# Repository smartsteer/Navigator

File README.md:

# SmartSteer Navigator

Aplikacja do prowadzenia równoległego i autosterowania ciągnika, zgodna z płytkami AgOpenGPS (AIO).
Jeden kod w Kotlinie daje dwie wersje:

- **Android** — tablet w kabinie (APK),
- **Windows** — komputer / tablet z Windows (instalator `.msi` / `.exe`).

## Jak to działa

Aplikacja liczy geometrię prowadzenia (linia AB, krzywe, pure pursuit) i co ok. 100 ms wysyła
zadany kąt skrętu do modułu na płytce. Regulację silnika (PID, PWM) i odczyt czujnika kąta kół
robi oryginalny firmware AgOpenGPS na płytce — nie jest zmieniany.

Komunikacja: UDP w sieci `192.168.5.x`, aplikacja nasłuchuje na porcie **9999**, wysyła na **8888**.
Ramka: `0x80 0x81 źródło PGN długość dane… CRC`.

| PGN | Kierunek | Treść |
|-----|----------|-------|
| 254 | aplikacja → moduł skrętu | prędkość, autoster wł./wył., kąt zadany, odległość od linii, sekcje |
| 253 | moduł skrętu → aplikacja | kąt rzeczywisty, kurs/przechył IMU, przełączniki, PWM |
| 252 / 251 | aplikacja → moduł skrętu | ustawienia i konfiguracja sterowania |
| 239 | aplikacja → moduł maszyny | sekcje, podnośnik, zawrót |

### Podłączenie tabletu z Androidem

Przejściówka USB‑C → Ethernet (najlepiej hub z ładowaniem PD) albo Wi‑Fi przez mały router
w kabinie. Router powinien rozdawać adresy (DHCP) w sieci `192.168.5.x`.

## Struktura

```
composeApp/
  src/commonMain/   wspólny kod: logika (core/) i ekrany (Compose Multiplatform)
  src/androidMain/  start aplikacji na Androidzie
  src/desktopMain/  start programu na Windowsie
  src/commonTest/   testy
```

## Budowanie

- Android: `./gradlew :composeApp:assembleDebug`
- Windows (na Windowsie): `./gradlew :composeApp:packageMsi`
- Uruchomienie na komputerze bez instalacji: `./gradlew :composeApp:run`
- Testy: `./gradlew :composeApp:desktopTest`

GitHub Actions budują APK i instalator Windows przy każdym pushu — pliki są w zakładce
**Actions → ostatni przebieg → Artifacts**.

## Plan

1. Rdzeń: odczyt NMEA, linia AB, odchyłka, symulator jazdy
2. Autosterowanie: pure pursuit, PGN 254/253, ekran diagnostyki
3. Sekcje i mapa pokrycia, zawroty, granice pól
4. Integracja z WAR (mapy aplikacyjne, ewidencja zabiegów)

## Licencja

GNU General Public License v3.0 (GPLv3). Projekt korzysta z rozwiązań i algorytmów AgOpenGPS
(© Brian Tischler i współtwórcy, GPLv3) — fragmenty przeniesione z AgOpenGPS są oznaczone w kodzie.
Program rozpowszechniany jest z kodem źródłowym, na tej samej licencji.

WAR (Wirtualny Asystent Rolnika) jest osobnym programem i nie jest objęty tą licencją —
wymienia dane z Navigatorem przez interfejs (mapy dawek, ewidencja zabiegów).

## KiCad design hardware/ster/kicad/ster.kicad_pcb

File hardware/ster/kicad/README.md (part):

# Płytka Ster — schemat jako kod (etap 15b)

Schemat płytki Ster w SKiDL → netlista KiCad. Specyfikacja: [`../README.md`](../README.md). Licencja GPLv3.
Na podstawie AgOpenGPS (© Brian Tischler i współtwórcy, GPLv3), pliki `TeensyModules/AIO Standard v4/PCB Build/AIO v4.5 Std/`
(PCB EasyEDA, „Ampseal pinout.jpg”) i `TeensyModules/AIO v4 Firmware/` z github.com/AgOpenGPS-Official/Boards.

| Plik | Co to |
|---|---|
| `ster.py` | schemat — źródło prawdy; `pip install skidl==1.2.3`, potem `python3 ster.py` → `ster.net` (bez bibliotek KiCad — wszystkie części zdefiniowane w kodzie) |
| `ster.net` | netlista KiCad (248 części, 208 sieci) do 15c |
| `imxrt1062_kulki.csv` | wszystkie 196 kulek MIMXRT1062 (MAPBGA‑196): kulka, sygnał, pin Teensy 4.1 |
| `bga196.py` → `smartsteer_ster.pretty` | obudowa MAPBGA‑196 12 × 12 mm / 0,8 mm (pola NSMD 0,40 mm); reszta obudów z bibliotek KiCad 7 |
| `place.py` | obrys 110 × 80 mm, 4 warstwy, rozmieszczenie (etap 15c1) |
| `netclass.py` | klasy połączeń: Default 0,15/0,127 mm (przelotka 0,45/0,2), Moc 1,2 mm, Zasilanie 0,4 mm, RF 0,35 mm, USB 0,2 mm |
| `ster.kicad_pcb`, `ster.kicad_pro` | płytka: części rozmieszczone, płaszczyzny In1 = GND, In2 = V3V3_STER; **bez ścieżek** (15c2) |

Kolejność (narzędzia: `../../narzedzia/README.md`): `ster.py` → `kinet2pcb -i ster.net -w -l .` → `netclass.py` → `place.py`
→ `plaszczyzny.py ster.kicad_pcb In1.Cu:GND In2.Cu:V3V3_STER` → (15c2) wyprowadzenie BGA, Freerouting, `dotrasuj.py`, wylewki mocy,
`drc.py`, `fab_jlcpcb.py`.

`ster.py` przy każdym uruchomieniu sprawdza (assert): AMPSEAL 1:1 z AIO v4.5 Std (poza 13 i 19 — CAN Maszyna), piny
Teensy z firmware AIO na tych samych kulkach co w Teensy 4.1, wszystkie kulki zasilania i masy podłączone; ERC bez uwag.

**Mapa kulek** pochodzi z `bga_pinout_t41` (PJRC, w repozytorium SparkFun MicroMod Teensy) i jest zgodna z kartą NXP
IMXRT1060CEC (tabele 86–87) dla wszystkich 196 kulek. Rdzeń (DCDC 1,1 V, kondensatory, kwarce 24 MHz / 32 kHz, flash QSPI
na SD_B1, bootloader MKL02 na JTAG/POR_B/BOOT_MODE0, kluczowanie 3,3 V przez PMIC_ON_REQ) odtworzony z połączeń
otwartego projektu SparkFun MicroMod Teensy (CC BY-SA 4.0) — czyli tak jak w Teensy 4.x, więc Teensy Loader działa.

## AMPSEAL 23 — ta sama wiązka co AIO v4.5 Std

| Pin | AIO v4.5 Std | Ster |
|---|---|---|
| 1 | 5V WAS | 5 V czujnika kąta (PTC 100 mA) |
| 2 / 3 | WAS High / Low | ADS1115 AIN0 / AIN1 (5 V, adres 0x48) |
| 4, 21, 23 | GND | masa |
| 5 / 6 | LEFT / RIGHT (Cytron) | wyjścia mostka DRV8701E |
| 7 | LOCK | AOD4185 z 12 V (5 A), dioda gasząca |
| 8 / 9 | Steer / Work | transoptory → piny 32 / 34, przyciski serwisowe |
| 10 | Pres/Rem | zworka: Remote (pin 37, domyślnie) albo ciśnienie (A10) |
| 11 / 12 | A12 / A13 | piny 26 / 27 przez zworki (zwarte) |
| 13 | A14 | **zmiana:** domyślnie CAN „Maszyna” L; zworka 2‑3 → A14 (pin 38) jak AIO |
| 14 / 15 | Speed + / − | transoptor od pinu 36 (otwarty kolektor; zworki: podciągnięcie 12 V, minus do masy) |
| 16 / 17 | CAN H / L | CAN3 (ciągnik / Keya), terminator zworką |
| 18 | Alt cytron pwr | zasilanie mostka; zworka z 12 V zwarta (otworzyć przy osobnym przewodzie) |
| 19 | — (wolny) | **CAN „Maszyna” H** (CAN2, piny 0/1) |
| 20 | +12 V Board | 12 V za idealną diodą |
| 22 | +12 V in | wejście 12 V |

Silnik zostaje na **jednym styku na fazę** (5, 6) i zasilanie 18 — jak AIO, żeby wiązka pasowała (w 15a było „2 + 2”,
ale AMPSEAL 23 nie ma wolnych pinów). Sprawdzić prąd styku przy przekroju przewodu (lista niżej).

## Piny Teensy → pad i.MXRT (te używane na płytce)

| Pin Teensy | Pad i.MXRT | Kulka BGA | Na płytce Ster |
|---|---|---|---|
| 0 | GPIO_AD_B0_03 | G11 | CAN2 RX → MCP2562 „Maszyna” |
| 1 | GPIO_AD_B0_02 | M11 | CAN2 TX → MCP2562 „Maszyna” |
| 2 | GPIO_EMC_04 | F2 | PWM silnika → DRV8701E EN |
| 3 | GPIO_EMC_05 | G5 | LOCK (2N7002 → AOD4185) + zworka nSLEEP |
| 4 | GPIO_EMC_06 | H5 | kierunek → DRV8701E PH |
| 5 | GPIO_EMC_08 | H3 | dioda: zasilanie |
| 6 | GPIO_B0_10 | D9 | dioda: Ethernet |
| 7 | GPIO_B1_01 | B11 | Serial2 RX (zapas) |
| 8 | GPIO_B1_00 | A11 | Serial2 TX (zapas) |
| 9 | GPIO_B0_11 | A10 | dioda: GPS czerwona |
| 10 | GPIO_B0_00 | D7 | dioda: GPS zielona |
| 11 | GPIO_B0_02 | E8 | dioda: autoster czuwanie |
| 12 | GPIO_B0_01 | E7 | dioda: autoster aktywny |
| 13 | GPIO_B0_03 | D8 | dioda: GGA |
| 14 | GPIO_AD_B1_02 | L11 | Serial3 TX → radio RTK |
| 15 | GPIO_AD_B1_03 | M12 | Serial3 RX ← radio RTK |
| 18 | GPIO_AD_B1_01 | K11 | I²C SDA → ADS1115 (translator 5 V) |
| 19 | GPIO_AD_B1_00 | J11 | I²C SCL → ADS1115 |
| 20 | GPIO_AD_B1_10 | L13 | Serial5 TX → IMU |
| 21 | GPIO_AD_B1_11 | J13 | Serial5 RX ← IMU (TM171 / BNO085 RVC) |
| 24 | GPIO_AD_B0_12 | K14 | A10 ciśnienie (dzielnik 10k/20k, 4–20 mA zworką) |
| 26 | GPIO_AD_B1_14 | G12 | A12 ← AMPSEAL 11 |
| 27 | GPIO_AD_B1_15 | J14 | A13 ← AMPSEAL 12 |
| 28 | GPIO_EMC_32 | D5 | Serial7 RX ← ZED‑F9P TXD |
| 29 | GPIO_EMC_31 | C5 | Serial7 TX → ZED‑F9P RXD |
| 30 | GPIO_EMC_37 | E4 | CAN3 RX (ciągnik / Keya) |
| 31 | GPIO_EMC_36 | C3 | CAN3 TX |
| 32 | GPIO_B0_12 | C10 | STEERSW ← transoptor |
| 33 | GPIO_EMC_07 | H4 | nFAULT DRV8701E (nowe, firmware 17) |
| 34 | GPIO_B1_13 | D14 | WORKSW ← transoptor |
| 36 | GPIO_B1_02 | C11 | impuls prędkości → transoptor |
| 37 | GPIO_B1_03 | D11 | REMOTE ← transoptor |
| 38 | GPIO_AD_B1_12 | H12 | A14 ← AMPSEAL 13 (zworka 2‑3) |
| 41 | GPIO_AD_B1_05 | K12 | A17 prąd silnika (SO DRV8701E, 60 mV/A) |

Ethernet RMII jak Teensy 4.1: GPIO_B1_04…B1_11, B1_14/B1_15 (MDC/MDIO), B0_14 reset, B0_15 power‑down, zegar 50 MHz
z GPIO_B1_10 do XI układu PHY. Flash QSPI: GPIO_SD_B1_06…11.

## Zmiany względem specyfikacji 15a

- Procesor **MIMXRT1062DVL6A** (12 × 12 mm, raster 0,8 mm) zamiast DVJ6A (to 10 × 10 mm, 0,65 mm — trudne na 4 warstwach JLCPCB).
  Rozkład kulek identyczny; Teensy 4.1 ma DVJ6A, firmware nie widzi różnicy.
- Przetwornica **LMR33620** (2 A, rodzina i piny jak LMR33610 na płytkach Maszyna; wejście do 36 V) zamiast LMR16020.
- LOCK na **AOD4185** (P‑MOSFET D‑PAK, jak Maszyna Lite) z Zenerem na bramce zamiast IRF5305 TO‑220.
- ADS1115 zasilany 5 V z translatorami I²C (2 × BSS138) — jak AIO, żeby czujnik kąta 0–5 V nie przekraczał zasilania ADC.
- Zasilanie z USB‑C przy programowaniu bez 12 V (dioda VBUS → 5 V).
- Dioda stanu przy każdym wejściu Steer/Work/Remote.

## Rozmieszczenie (15c1, 2026-11-28)

Płytka **110 × 80 mm** (w 15a cel 100 × 75 — nie zmieściło się z AMPSEAL 23 o szerokości 61 mm i dwoma kondensatorami
1000 µF; Hammond 1455N2201 ma 103 × 160 wewnątrz — do potwierdzenia przy obudowie).
- Dół: AMPSEAL 23 (krawędź obudowy na krawędzi płytki), nad nim mostek silnika (4 × BUK7J1R4) i DRV8701E, LOCK (AOD4185) z lewej.
- Prawy dół: wejście 12 V (idealna dioda 2 × BUK7J1R4 + LM74700, TVS SMCJ24A), LMR33620 z dławikiem, 2 × 1000 µF przy krawędzi.
- Góra: RJ45 (lewy róg), USB‑C procesora, USB‑C GPS, SMA anteny (prawy róg, nad ZED‑F9P). Prawa krawędź: JST GH radio RTK i IMU.
- Środek: i.MXRT1062 (strefa 16 × 16 mm wolna od drobnych części na wyprowadzenie BGA), flash, MKL02, kwarce, DP83825I między procesorem a RJ45.

Zmiany obudów: RJ45 **HR911105A** (LCSC C12074, jest w bibliotece KiCad) zamiast HR913550A; przyciski TS‑1187A na footprincie
**TL3342** (5,2 × 5,2 mm, 4 pady — TS‑1187A ma ten sam rozstaw, sprawdzić przy zakupie); DP83825I na QFN‑24 3 × 3 mm 0,4 mm,
pole 1,75 × 1,6 mm (sprawdzić z rysunkiem RMQ0024A).

DP83825I — numery pinów z karty TI SNLS638C (tabela 4‑1). Tryb RMII „follower” jak Teensy 4.1: 50 MHz z procesora na XI (13),
XO (12) i pin 2 wolne; biblioteki NativeEthernet/QNEthernet same ustawiają rejestr RCSR (0x17) = 0x0081. Paski (piny 2, 4, 17,
18, 20, 22) zostają na wewnętrznych ściągnięciach jak w Teensy 4.1 (adres PHY 0).

## Do sprawdzenia (przed 15c i przez elektronika)

1. RJ45 HR911105A: piny diod 9–12 (zielona 11/12, żółta 9/10) z karty producenta przed zamówieniem.
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
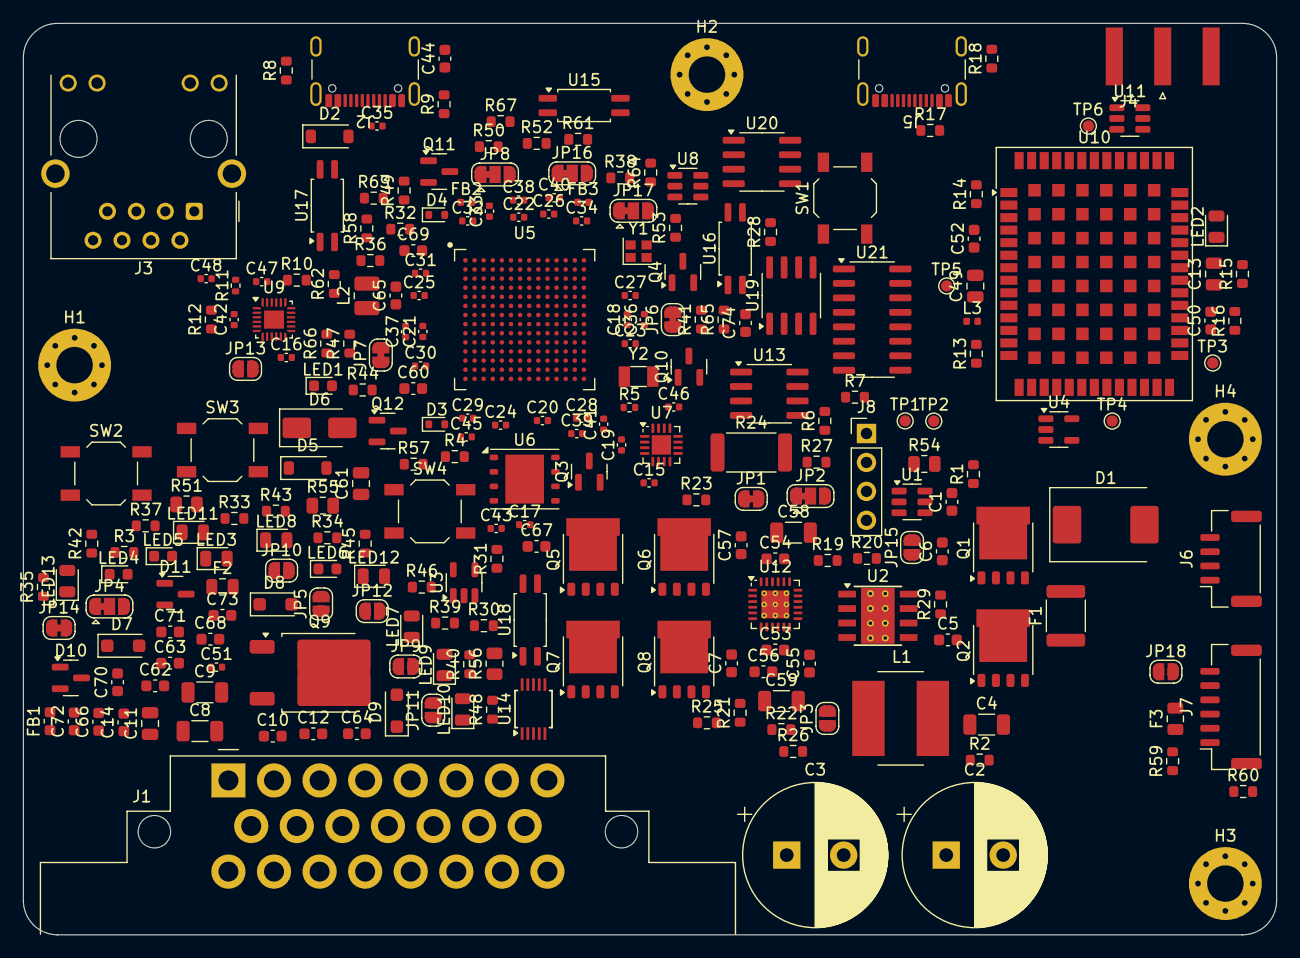
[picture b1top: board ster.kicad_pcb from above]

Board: 4 copper layers, 110.0 x 80.0 mm, 249 parts (0 on the bottom side), 208 nets, no tracks yet.

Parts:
C1, C6, C14, C62, C63, C64, C65, C66, C67, C68, C69, C70, C71, C72, C73, C74: 100n; C_0603_1608Metric
C2, C3: 1000u 35V (jak AIO); CP_Radial_D12.5mm_P5.00mm
C4, C58, C59: 10u 50V; C_1206_3216Metric
C5, C54, C57: 100n 50V; C_0603_1608Metric
C7, C10, C12, C44, C52, C55, C56: 1u; C_0603_1608Metric
C8, C9: 22u 10V; C_1206_3216Metric
C11, C13, C49: 10u; C_0805_2012Metric
C15, C35: 2.2u; C_0402_1005Metric
C16, C21, C25, C28, C30: 4.7u; C_0402_1005Metric
C17, C18, C22, C24, C27, C29, C31, C32, C34, C36, C37: 0.22u; C_0402_1005Metric
C19, C23, C51: 10n; C_0402_1005Metric
C20, C26, C33: 10u; C_0402_1005Metric
C38, C39: 12p; C_0402_1005Metric
C40, C41: 20p; C_0402_1005Metric
C42, C43, C46, C47, C48: 0.1u; C_0402_1005Metric
C45: 1u; C_0402_1005Metric
C50: 0.1u; C_0603_1608Metric
C53: 1u 16V; C_0603_1608Metric
C60: 10n; C_0603_1608Metric
C61: 1u 25V; C_0805_2012Metric
D1: SMCJ24A; D_SMC
D2: SS14 / B5819W (VBUS→5 V); D_SOD-123
D3, D4: RB751S40; D_SOD-523
D5: BZT52C15 (ochrona bramki); D_SOD-123
D6: SS34 (gaszenie cewki LOCK); D_SMA
D7, D8, D9: SS14 (jak AIO); D_SOD-123F
D10, D11: PESD1CAN,215; SOT-23
F1: PTC 1,1 A; Fuse_1812_4532Metric
F2: PTC 100 mA (czujnik kąta); Fuse_0805_2012Metric
F3: PTC 200 mA; Fuse_0805_2012Metric
FB1: 600R@100MHz; L_0603_1608Metric
FB2, FB3: 120R@100MHz; L_0402_1005Metric
H1, H2, H3, H4: M3 (masa); MountingHole_3.2mm_M3_Pad_Via
J1: AMPSEAL 23 (776087-1) — wiązka AIO; TE_AMPSEAL_1-776087-x_3Rows_23_P0.4mm_Horizontal
J2: USB-C procesor (AgIO, wgrywanie); USB_C_Receptacle_GCT_USB4105-xx-A_16P_TopMnt_Horizontal
J3: HR911105A (RJ45 z transformatorem); RJ45_Hanrun_HR911105A_Horizontal
J4: SMA krawędziowe — antena GNSS; SMA_Amphenol_132289_EdgeMount
J5: USB-C GPS (u-center); USB_C_Receptacle_GCT_USB4105-xx-A_16P_TopMnt_Horizontal
J6: Radio RTK (Serial3, 115200); JST_GH_SM04B-GHS-TB_1x04-1MP_P1.25mm_Horizontal
J7: IMU TM171 / BNO085 RVC (Serial5); JST_GH_SM06B-GHS-TB_1x06-1MP_P1.25mm_Horizontal
J8: Serial2 zapas (nie montować); PinHeader_1x04_P2.54mm_Vertical
JP1: SILNIK z V12 — otworzyć przy osobnym zasilaniu si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; SolderJumper-2_P1.3mm_Bridged_RoundedPad1.0x1.5mm
JP2: nSLEEP: 1‑2 stale (domyślnie) / 2‑3 od pinu 3 (si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; SolderJumper-3_P1.3mm_Bridged12_RoundedPad1.0x1.5mm
JP3: DANFOSS → LEFT (tylko bez mostka silnika) (otwart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; SolderJumper-2_P1.3mm_Open_RoundedPad1.0x1.5mm
JP4: PRES/REM (AMPSEAL 10): 1‑2 Remote (domyślnie) / 2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; SolderJumper-3_P1.3mm_Bridged12_RoundedPad1.0x1.5mm
JP5: 4–20 mA (otwarta); SolderJumper-2_P1.3mm_Open_RoundedPad1.0x1.5mm
JP6: A12B (zwarta); SolderJumper-2_P1.3mm_Bridged_RoundedPad1.0x1.5mm
JP7: A13B (zwarta); SolderJumper-2_P1.3mm_Bridged_RoundedPad1.0x1.5mm
JP8: AMPSEAL 13: 1‑2 CAN Maszyna L (domyślnie) / 2‑3 A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; SolderJumper-3_P1.3mm_Bridged12_RoundedPad1.0x1.5mm
JP9: SPEED+ podciągnięcie do 12 V (otwarta); SolderJumper-2_P1.3mm_Open_RoundedPad1.0x1.5mm
JP10: SPEED- do masy (otwarta); SolderJumper-2_P1.3mm_Open_RoundedPad1.0x1.5mm
JP11: terminator CAN3 (otwarta); SolderJumper-2_P1.3mm_Open_RoundedPad1.0x1.5mm
JP12: terminator CAN2 (otwarta); SolderJumper-2_P1.3mm_Open_RoundedPad1.0x1.5mm
JP13: IMU 3,3 V (otwarta); SolderJumper-2_P1.3mm_Open_RoundedPad1.0x1.5mm
JP14: IMU 5 V (zwarta); SolderJumper-2_P1.3mm_Bridged_RoundedPad1.0x1.5mm
JP15: IMU 12 V (otwarta); SolderJumper-2_P1.3mm_Open_RoundedPad1.0x1.5mm
JP16: IMU RX: 1‑2 TTL (domyślnie) / 2‑3 RS232; SolderJumper-3_P1.3mm_Bridged12_RoundedPad1.0x1.5mm
JP17: IMU TX: 1‑2 TTL (domyślnie); SolderJumper-3_P1.3mm_Bridged12_RoundedPad1.0x1.5mm
JP18: IMU TX RS232 (przy RS232 przeciąć 1‑2 wyżej) (otw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; SolderJumper-2_P1.3mm_Open_RoundedPad1.0x1.5mm
L1: 10uH 3A; L_Bourns_SRN8040TA
L2: 4.7uH (DCDC rdzenia); L_1008_2520Metric
L3: 47nH (zasilanie anteny); L_0402_1005Metric
LED1: żółta — bootloader; LED_0603_1608Metric
LED2: RTK (świeci = FIX); LED_0805_2012Metric
LED3: GPS 1PPS; LED_0805_2012Metric
LED4: STEER; LED_0603_1608Metric
LED5: WORK; LED_0603_1608Metric
LED6: REMOTE; LED_0603_1608Metric
LED7: zasilanie; LED_0805_2012Metric
LED8: Ethernet; LED_0805_2012Metric
LED9: GPS czerwona; LED_0805_2012Metric
LED10: GPS zielona; LED_0805_2012Metric
LED11: autoster czuwanie; LED_0805_2012Metric
LED12: autoster aktywny; LED_0805_2012Metric
LED13: GGA; LED_0805_2012Metric
Q1, Q2, Q5, Q6, Q7, Q8: BUK7J1R4-40H; LFPAK56
Q3: DMG2305UX; SOT-23
Q4, Q10: 2N7002; SOT-23
Q9: AOD4185 (zamiast IRF5305); TO-252-2
Q11, Q12: BSS138; SOT-23
R1, R3, R4, R6, R16, R29, R32, R52: 100k; R_0603_1608Metric
R2: 24k9; R_0603_1608Metric
R5: 2.2M; R_0402_1005Metric
R7, R14, R15, R27, R34, R35, R40, R43, R46, R61, R62, R63, R64, R65, R66, R67: 1k; R_0603_1608Metric
R8, R9, R17, R18: 5.1k; R_0603_1608Metric
R10: 1.5k; R_0603_1608Metric
R11: 6.49k 1%; R_0402_1005Metric
R12: 470; R_0603_1608Metric
R13: 10; R_0603_1608Metric
R19, R22, R23, R25, R26, R28, R30, R36, R37, R38, R39, R41, R44, R47, R49: 10k; R_0603_1608Metric
R20: 4.7k; R_0603_1608Metric
R21: 200k; R_0603_1608Metric
R24: 3m 3W; R_2512_6332Metric
R31, R42, R45, R48: 2.2k; R_0603_1608Metric
R33, R57, R58, R59, R60: 100; R_0603_1608Metric
R50: 20k; R_0603_1608Metric
R51: 250 0.1%; R_0805_2012Metric
R53: 330; R_0603_1608Metric
R54: 2.2k; R_0805_2012Metric
R55, R56: 120; R_0805_2012Metric
SW1: PROGRAM; SW_SPST_TL3342
SW2: serwis STEER; SW_SPST_TL3342
SW3: serwis WORK; SW_SPST_TL3342
SW4: serwis REMOTE; SW_SPST_TL3342
TP1: SWD_CLK; TestPoint_Pad_D1.0mm
TP2: SWD_DIO; TestPoint_Pad_D1.0mm
TP3: GPS RESET; TestPoint_Pad_D1.0mm
TP4: GPS SAFEBOOT; TestPoint_Pad_D1.0mm
TP5: GPS UART2 TX; TestPoint_Pad_D1.0mm
TP6: GPS UART2 RX; TestPoint_Pad_D1.0mm
U1: LM74700QDBVRQ1; SOT-23-6
U2: LMR33620ADDAR; Texas_HSOP-8-1EP_3.9x4.9mm_P1.27mm_ThermalVias
U3: TLV75733PDBVR (3,3 V procesor); SOT-23-5
U4: TLV75733PDBVR (3,3 V GNSS); SOT-23-5
U5: MIMXRT1062DVL6A; NXP_MAPBGA-196_12x12mm_P0.8mm
U6: W25Q64JVZPIQ (8 MB); WSON-8-1EP_6x5mm_P1.27mm_EP3.4x4.3mm
U7: PJRC MKL02 (bootloader Teensy); QFN-16-1EP_3x3mm_P0.5mm_EP1.7x1.7mm
U8, U11: USBLC6-2SC6; SOT-23-6
U9: DP83825IRMQR; QFN-24-1EP_3x3mm_P0.4mm_EP1.75x1.6mm
U10: ZED-F9P-04B; ublox_ZED
U12: DRV8701ERGER; VQFN-24-1EP_4x4mm_P0.5mm_EP2.45x2.45mm_ThermalVias
U13: TC4427AEOA (Danfoss, NIE MONTOWAĆ domyślnie); SOIC-8_3.9x4.9mm_P1.27mm
U14: ADS1115IDGSR; TSSOP-10_3x3mm_P0.5mm
U15, U16, U17, U18: EL3H7(B)(TA)-G; SOP-4_4.4x2.6mm_P1.27mm
U19: MCP2562-E/SN (CAN3); SOIC-8_3.9x4.9mm_P1.27mm
U20: MCP2562-E/SN (CAN2); SOIC-8_3.9x4.9mm_P1.27mm
U21: MAX3232EIDR (NIE MONTOWAĆ — tylko gdy TM171 ma RS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; SOIC-16_3.9x9.9mm_P1.27mm
Y1: 24 MHz; Crystal_SMD_2016-4Pin_2.0x1.6mm
Y2: 32.768 kHz; Crystal_SMD_3215-2Pin_3.2x1.5mm

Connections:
A12B: J1.11, JP6.1
A12B_MCU: JP6.2, U5.G12
A13B: J1.12, JP7.1
A13B_MCU: JP7.2, U5.J14
A14_MCU: JP8.3, R52.1, U5.H12
AMP13_A14_CAN2L: J1.13, JP8.2
BL_LED: R7.1, U7.11
BOOT_MODE0: U5.F11, U7.4
BUCK_BOOT: C6.1, U2.7
BUCK_FB: R1.2, R2.1, U2.5
BUCK_SW: C6.2, L1.1, U2.8
BUCK_VCC: C7.1, U2.6
CAN2_MASZYNA_H: D11.2, J1.19, R56.1, U20.7
CAN2_MASZYNA_L: D11.1, JP8.1, JP12.2, U20.6
CAN2_RX: U5.G11, U20.4
CAN2_TX: U5.M11, U20.1
CAN3_H: D10.2, J1.16, R55.1, U19.7
CAN3_L: D10.1, J1.17, JP11.2, U19.6
CAN3_RX: U5.E4, U19.4
CAN3_TX: U5.C3, U19.1
DANFOSS_OUT: R33.1, U13.7
DCDC_IN: C20.1, C21.1, C22.1, FB2.2, U5.L1, U5.L2
DCDC_LP: L2.1, U5.M1, U5.M2
DEBUG_EN: U5.F3, U7.15
DEBUG_SWO: U5.D10, U7.12
ENET_CRS_DV: U5.C12, U9.20
ENET_MDC: U5.C14, U9.16
ENET_MDIO: R10.2, U5.B14, U9.15
ENET_PWDN: U5.E11, U9.3
ENET_REF_CLK_50M: U5.B13, U9.13
ENET_RST: U5.E10, U9.5
ENET_RX0: U5.E12, U9.18
ENET_RX1: U5.D12, U9.17
ENET_RX_ER: U5.C13, U9.22
ENET_TX0: U5.B12, U9.23
ENET_TX1: U5.A12, U9.24
ENET_TX_EN: U5.A13, U9.1
ETH_CT: C48.1, J3.4, J3.5
ETH_LED_LINK: R12.1, U9.4
ETH_RD_M: J3.6, U9.7
ETH_RD_P: J3.3, U9.8
ETH_TD_M: J3.2, U9.10
ETH_TD_P: J3.1, U9.11
GND: C2.2, C3.2, C4.2, C5.2, C7.2, C8.2, C9.2, C10.2, C11.2, C12.2, C13.2, C14.2, C15.2, C16.2, C17.2, C18.2, C19.2, C20.2, C21.2, C22.2, C23.2, C24.2, C25.2, C26.2, C27.2, C28.2, C29.2, C30.2, C31.2, C32.2, C33.2, C34.2, C35.2, C36.2, C37.2, C38.2, C39.2, C40.2, C41.2, C42.2, C43.2, C44.2, C45.2, C46.2, C47.2, C48.2, C49.2, C50.2, C51.2, C52.2, C55.2, C56.2, C57.2, C58.2, C59.2, C60.2, C61.2, C62.2, C63.2, C64.2, C65.2, C66.2, C67.2, C68.2, C69.2, C72.2, C73.2, C74.2, D1.2, D6.2, D10.3, D11.3, H1.1, H2.1, H3.1, H4.1, J1.4, J1.21, J1.23, J2.A1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
GNSS_RF: J4.1, L3.2, U10.2
GNSS_VCC_RF: R13.1, U10.7
GPS_RESET: TP3.1, U10.49
GPS_RTK_STAT: LED2.1, U10.20
GPS_RXD2: TP6.1, U10.26
GPS_RX_SERIAL7_TX: U5.C5, U10.43
GPS_SAFEBOOT: TP4.1, U10.50
GPS_TIMEPULSE: R15.1, U10.53
GPS_TXD2: TP5.1, U10.27
GPS_TX_SERIAL7_RX: U5.D5, U10.42
GPS_USB_DM: J5.A7, J5.B7, U10.39, U11.3, U11.4
GPS_USB_DP: J5.A6, J5.B6, U10.40, U11.1, U11.6
GPS_VBUS: C52.1, J5.A4, J5.A9, J5.B4, J5.B9, R16.1, U10.38, U11.5
ID_GATE: Q1.4, Q2.4, U1.5
ID_VCAP: C1.1, U1.1
IMU_R1OUT: JP16.3, U21.12
IMU_RX_LINIA: J7.4, JP18.2, R60.2
IMU_T1OUT: JP18.1, U21.14
IMU_TX_LINIA: J7.3, R59.1, U21.13
JTAG_MOD: U5.F13, U7.13
JTAG_TCK: U5.F12, U7.8
JTAG_TDI: U5.F14, U7.7
JTAG_TDO: U5.G13, U7.6
JTAG_TMS: U5.E14, U7.5
JTAG_TRST: R6.1, U5.G10, U5.K3, U7.3
LED_PIN5: R61.1, U5.H3
LED_PIN6: R62.1, U5.D9
LED_PIN9: R63.1, U5.A10
LED_PIN10: R64.1, U5.D7
LED_PIN11: R65.1, U5.E8
LED_PIN12: R66.1, U5.E7
LED_PIN13: R67.1, U5.D8
LOCK: C61.1, D6.1, J1.7, Q9.2, U13.6
LOCK_G: D5.2, Q9.1, R30.2, R31.1
LOCK_G_STER: Q10.3, R31.2
MOT_AVDD: C55.1, R19.1, U12.7
MOT_BOCZNIK: Q6.1, Q6.2, Q6.3, Q8.1, Q8.2, Q8.3, R24.1, U12.21
MOT_CPH: C54.1, U12.3
MOT_CPL: C54.2, U12.4
MOT_DIR_PIN4: R26.1, U5.H5, U12.15
MOT_DVDD: C56.1, R22.1, U12.8
MOT_PRAD_A17: C60.1, R27.2, U5.K12
MOT_PWM_PIN2: R25.1, U5.F2, U12.14, U13.2
MOT_SNSOUT: R22.2, U12.10
MOT_SO: R27.1, U12.11
MOT_VCP: C53.1, U12.2
MOT_VREF: R19.2, R20.1, U12.6
MOT_nFAULT: R23.2, U5.H4, U12.9
MOT_nSLEEP: JP2.2, R29.1, U12.13
unnamed: LED1.1, R7.2
unnamed: J2.A5, R8.1
unnamed: J2.B5, R9.1
unnamed: R11.1, U9.14
unnamed: J3.12, R12.2
unnamed: C51.1, L3.1, R13.2
unnamed: LED2.2, R14.2
unnamed: LED3.2, R15.2
unnamed: J5.A5, R17.1
unnamed: J5.B5, R18.1
unnamed: R21.1, U12.12
unnamed: Q5.4, U12.17
unnamed: Q6.4, U12.19
unnamed: Q7.4, U12.24
unnamed: Q8.4, U12.22
unnamed: JP3.1, R33.2
unnamed: LED4.2, R42.2
unnamed: LED5.2, R45.2
unnamed: LED6.2, R48.2
unnamed: JP5.1, R51.2
unnamed: R53.2, U18.1
unnamed: JP9.1, R54.2
unnamed: JP11.1, R55.2
unnamed: JP12.1, R56.2
unnamed: J6.3, R57.1
unnamed: J6.4, R58.2
unnamed: F3.1, JP13.2, JP14.2, JP15.2
unnamed: C70.1, U21.1
unnamed: C70.2, U21.3
unnamed: C71.1, U21.4
unnamed: C71.2, U21.5
unnamed: C72.1, U21.2
unnamed: C73.1, U21.6
unnamed: JP16.1, R59.2
unnamed: JP17.1, R60.1
unnamed: LED7.2, R61.2
unnamed: LED8.2, R62.2
unnamed: LED9.2, R63.2
unnamed: LED10.2, R64.2
unnamed: LED11.2, R65.2
unnamed: LED12.2, R66.2
unnamed: LED13.2, R67.2
NVCC_PLL: C27.1, C28.1, U5.P10
PMIC_ON_REQ: Q4.1, R4.2, U5.K7
POR_B: U5.M7, U7.9
PRESSURESENSE: JP4.3, R49.1, R51.1
PRESSURE_A10: C65.1, R49.2, R50.1, U5.K14
PRES_REM: J1.10, JP4.2
PROGRAM: SW1.1, U7.10
PWM2_PIN3: JP2.3, Q10.1, R32.1, U5.G5
QSPI_B1_06: U5.L3, U6.1
QSPI_B1_07: U5.L4, U6.6
QSPI_B1_08: U5.P3, U6.5
QSPI_B1_09: U5.N4, U6.2
QSPI_B1_10: U5.P4, U6.3
QSPI_B1_11: U5.P5, U6.7
RADIO_DO_SERIAL3_RX: R57.2, U5.M12
REMOTEPIN: D9.1, JP4.1, SW4.1
REMOTE_A: R46.2, U17.1
REMOTE_K: D9.2, LED6.1, U17.2
REMOTE_WE: R47.2, U5.D11, U17.4
RTC_XTALI: C40.1, U5.N9, Y2.1
RTC_XTALO: C41.1, U5.P9, Y2.2
SCL: Q12.2, R38.2, U5.J11
SCL_5V: Q12.3, R39.2, U14.10
SDA: Q11.2, R36.2, U5.K11
SDA_5V: Q11.3, R37.2, U14.9
SERIAL2_RX: J8.3, U5.B11
SERIAL2_TX: J8.4, U5.A11
SERIAL3_TX_DO_RADIA: R58.1, U5.L11
SERIAL5_RX: JP16.2, U5.J13
SERIAL5_TX: JP17.2, U5.L13, U21.11
SILNIK_LEFT: J1.5, JP3.2, Q5.1, Q5.2, Q5.3, Q6.5, U12.18
SILNIK_RIGHT: J1.6, Q7.1, Q7.2, Q7.3, Q8.5, U12.23
SPEED_MINUS: J1.15, JP10.1, U18.3
SPEED_PLUS: J1.14, JP9.2, U18.4
SPEED_PWM_PIN36: R53.1, U5.C11
STEERPIN: D7.1, J1.8, SW2.1
STEER_A: R40.2, U15.1
STEER_K: D7.2, LED4.1, U15.2
STEER_WE: R41.2, U5.C10, U15.4
SWD_CLK: TP1.1, U7.14
SWD_DIO: TP2.1, U7.16
USB1_DN: J2.A7, J2.B7, U5.M8, U8.3, U8.4
USB1_DP: J2.A6, J2.B6, U5.L8, U8.1, U8.6
USB_VBUS: C35.1, C44.1, D2.2, FB3.1, J2.A4, J2.A9, J2.B4, J2.B9, U8.5
USB_VBUS_MCU: C36.1, C37.1, FB3.2, U5.N6, U5.P6
V3V3: C11.1, D3.2, Q3.2, R3.1, U3.5
V3V3_GNSS: C13.1, C49.1, C50.1, R14.1, U4.5, U10.33, U10.34, U10.36
V3V3_STER: C15.1, C16.1, C17.1, C18.1, C19.1, C42.1, C43.1, C45.1, C46.1, C47.1, C67.1, C69.1, C74.1, FB2.1, J3.11, J8.1, JP13.1, LED1.2, Q3.3, Q11.1, Q12.1, R4.1, R10.1, R23.1, R28.1, R36.1, R38.1, R41.1, R44.1, R47.1, U5.E6, U5.E9, U5.F5, U5.F10, U5.J6, U5.J10, U5.K4, U5.K5, U5.N14, U5.P12, U6.8, U7.1, U9.6, U9.19, U19.5, U20.5, U21.16
V3_KLUCZ_G: Q3.1, Q4.3, R3.2
V5: C8.1, C9.1, C10.1, C62.1, C66.1, C68.1, D2.1, F2.1, FB1.1, J6.1, JP14.1, L1.2, R1.1, R37.1, R39.1, R40.1, R42.1, R43.1, R45.1, R46.1, R48.1, U3.1, U3.3, U14.8, U19.3, U20.3
V5_GNSS: C12.1, FB1.2, U4.1, U4.3
V5_WAS: C14.1, F2.2, J1.1
V12: C2.1, C3.1, D1.1, D5.1, F1.1, J1.20, JP1.1, JP15.1, Q1.5, Q2.5, Q9.3, R30.1, R54.1, U1.4
V12_FILTR: C4.1, C5.1, F1.2, U2.2, U2.3
V12_SILNIK: C53.2, C57.1, C58.1, C59.1, J1.18, JP1.2, Q5.5, Q7.5, U12.1
VCC_IMU: F3.2, J7.1
VDD_HIGH_CAP: C29.1, C30.1, U5.P8
VDD_SNVS_CAP: C31.1, U5.M10
VDD_SNVS_IN: C34.1, D3.1, D4.1, U5.M9
VDD_SOC_IN: C23.1, C24.1, C25.1, C26.1, L2.2, U5.F6, U5.F7, U5.F8, U5.F9, U5.G6, U5.G9, U5.H6, U5.H9, U5.J5, U5.J9
VDD_USB_CAP: C32.1, C33.1, D4.2, U5.K8
VIN_12V: C1.2, J1.22, Q1.1, Q1.2, Q1.3, Q2.1, Q2.2, Q2.3, U1.3, U1.6
WAS_H: J1.2, R34.1
WAS_H_ADC: C63.1, R34.2, U14.4
WAS_L: J1.3, R35.1
WAS_L_ADC: C64.1, R35.2, U14.5
WORKPIN: D8.1, J1.9, SW3.1
WORK_A: R43.2, U16.1
WORK_K: D8.2, LED5.1, U16.2
WORK_WE: R44.2, U5.D14, U16.4
XTALI: C38.1, R5.1, U5.P11, Y1.1
XTALO: C39.1, U5.N11, Y1.2
nSLEEP_3V3: JP2.1, R28.2

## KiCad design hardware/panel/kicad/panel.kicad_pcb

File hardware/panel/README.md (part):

# Panel przełączników opryskiwacza (bezprzewodowy, 6 × AA) — specyfikacja (etap 22a)

Zewnętrzny panel do przypięcia w kabinie w dowolnym miejscu: przełączniki sekcji jak w klasycznym terminalu,
diody RGB pokazujące to samo co Navigator, pokrętło dawki. Bez kabla — zasilanie z 6 baterii AA.
Wizualizacja: [wersja 2 — pod dłoń, e‑papier, roller](wizualizacja_v2.png) (aktualna), [wersja 1](wizualizacja.png).
Licencja GPLv3. **Przed zamówieniem projekt przegląda elektronik** (lista „Do sprawdzenia” na końcu).

Decyzje właściciela (2026-11-20): przełączniki dźwigniowe IP67, diody RGB w stylu ekranu Navigatora,
pokrętło do dawki, 6 × AA, płytka w całości montowana w JLCPCB, nowoczesna opływowa obudowa (własny projekt).

## Wersja 2 (decyzja właściciela 2026-11-20)

- **Obudowa pod dłoń**: z prawej wyprofilowane podparcie dłoni (miękka nakładka); kciuk: roller dawki i START/STOP, palce: dźwignie sekcji.
  Wersja dla leworęcznych — lustrzana obudowa, ta sama płytka.
- **Roller zamiast pokrętła**: kółko pod kciuk z magnesami, czujniki Halla pod zamkniętą ścianką (bez otworu → łatwe IP67; zamiast AS5600 — patrz obudowa/README.md);
  wciśnięcie (mikroprzełącznik pod uszczelką) = powrót do dawki zadanej.
- **Wyświetlacz e‑papier 4,2"** (np. moduł SPI 400 × 300): dawka zadana/rzeczywista, ciśnienie, zbiornik, hektary, prędkość;
  czytelny w słońcu, prąd tylko przy odświeżeniu (co 2–5 s przy pracy) — bilans baterii prawie bez zmian.
- **Dźwignie sekcji chwilowe** (samopowrót do środka): w górę = włącz, w dół = wyłącz. Stan pokazuje tylko dioda —
  **zielona** = pryska, **żółta** = wyłączona przez automat (pokrycie, granica, uwrocie), **ciemna** = wyłączona,
  **czerwona** = błąd zaworu sekcji. Nie ma już niezgodności dźwignia ↔ ekran (miganie niepotrzebne), a dźwignie w spoczynku
  nie pobierają prądu. Zmiana z tabletu po prostu zmienia diodę.
- **Włącznik zasilania** (kołyskowy I/O, uszczelniony) — odcina baterie całkowicie; panel wraca do ostatnio połączonej płytki.
- **Montaż „włóż, skręć, działa”** (decyzja właściciela 2026-11-20): każdy panel ma **własną płytkę**, wymiarami i położeniem
  otworów dokładnie pod swoją obudowę — dźwignie, przyciski, roller, diody i e‑papier są wlutowane w płytkę (JLCPCB),
  płytkę trzymają nakrętki dźwigni + 4 wkręty, baterie jedną wtyczką z komory. Zero przewodów do lutowania.
  Wspólny jest **schemat bloków** (procesor, zasilanie, sterownik diod, BLE) i **firmware** — płytka rozpoznaje sama,
  czy jest panelem oprysku, czy hydrauliki (rezystor identyfikacyjny na płytce).
- ~~Ta sama płytka panelu~~ Panel hydrauliki ma osobną płytkę o tym samym schemacie bloków — **panelu hydrauliki** (hardware/hydraulika) — inna płyta czołowa i firmware.

## Elementy na panelu

| Element | Ile | Działanie |
|---|---|---|
| Przełącznik dźwigniowy sekcji, IP67 (ON‑OFF) | 1–13 | góra = sekcja dozwolona (AUTO w Navigatorze), dół = sekcja wyłączona na stałe |
| Dioda RGB przy każdej sekcji | 1–13 | **zielona** = sekcja pryska, **żółta** = wyłączona przez automat (pokrycie, granica, uwrocie), **czerwona** = wyłączona przełącznikiem / na ekranie, **miga** = stan na ekranie inny niż dźwignia (np. zmieniony z tabletu) |
| Przycisk START/STOP z podświetlanym pierścieniem, IP67 | 1 | to samo co duży przycisk na ekranie Oprysk (zawór główny) |
| Przełącznik AUTO / RĘCZNIE (regulacja dawki) | 1 | jak na ekranie |
| Przełącznik oświetlenia roboczego | 1 | jak na ekranie |
| Roller pod kciuk (magnes + AS5600), z wciśnięciem | 1 | obrót: dawka ±5 % (AUTO) albo impulsy zaworu regulacyjnego (RĘCZNIE); wciśnięcie: powrót do dawki zadanej |
| Dioda stanu RGB | 1 | łączność (zielona), szukanie (niebieska miga), bateria słaba (żółta), brak łączności (czerwona) |
| Czujnik światła | 1 | jasność diod: pełna w dzień, przygaszona w nocy |

Płytka zawsze z 13 miejscami na sekcje (jak płytka Maszyna) — w obudowie zaślepki tam, gdzie opryskiwacz ma mniej sekcji.

## Łączność

```
Panel (ESP32‑C3, BLE) ──Bluetooth LE──► płytka Maszyna (ESP32, BLE obok Bluetooth SPP) ──PGN 161/162──► Navigator
                       ◄── stan diod ──                                                  ◄──PGN 160/163──
```

- Panel łączy się z **płytką Maszyna**, nie z tabletem: działa z Windows bez Bluetootha, z USB, z płytką Ster po CAN.
- Parowanie: przytrzymanie START/STOP przy włożeniu baterii → panel szuka; w Navigatorze „Oprysk → Ustawienia → Panel: Paruj”.
- Navigator jest jedynym „szefem” stanu: panel zgłasza zmianę dźwigni / przycisku / pokrętła, Navigator ją przyjmuje
  i odsyła stan wszystkich diod. Dzięki temu ekran i panel zawsze pokazują to samo.
- **Bezpieczeństwo:** brak łączności z panelem nic nie wyłącza ani nie włącza — sterowanie zostaje na ekranie,
  Navigator pokazuje „panel niedostępny”. Dźwignia w dół zawsze wygrywa (sekcja wyłączona), także gdy ekran mówi inaczej.
- Nowe ramki (szczegóły w etapie 22d, docs/MASZYNA.md): PGN 162 panel → Navigator (dźwignie, przyciski, kroki pokrętła,
  bateria), PGN 163 Navigator → panel (kolory diod, jasność). Po CAN: 0x384 / 0x385.

## Zasilanie — 6 × AA

- 6 × AA szeregowo: 9 V (alkaliczne 6,0–9,6 V; akumulatory NiMH 6 × 1,2 V = 7,2 V też działają).
- Przetwornica obniżająca 3,3 V z bardzo małym poborem własnym (TPS62177, ~5 µA), ochrona przed odwrotnym włożeniem
  baterii (MOSFET P), pomiar napięcia baterii dzielnikiem z kluczem (prąd płynie tylko przy pomiarze).
- Przełączniki: rezystory podciągające 1 MΩ (dźwignia „włączona” pobiera 3,3 µA, a nie 330 µA przy 10 k).
- Diody: zwykłe diody RGB (nie WS2812 — te pobierają ~1 mA każda, nawet zgaszone) sterowane z **2 × IS31FL3236A**
  (36 kanałów PWM po I²C, w uśpieniu ~1 µA) — 14 diod × 3 kolory = 42 kanały.

| Stan | Pobór (szacunek) |
|---|---|
| praca, diody w dzień (14 × ~2 mA) + BLE | ~30 mA z 3,3 V ≈ 100 mW |
| praca, diody w nocy (przygaszone) | ~8 mA ≈ 30 mW |
| uśpienie (STOP > 10 min albo brak Navigatora > 1 min) | ~15 µA |

6 × AA alkaliczne ≈ 20 Wh użytecznej energii → **ok. 200 h pracy w dzień, ponad 500 h nocą** (orientacyjnie — do
potwierdzenia na prototypie). To z grubsza sezon oprysków; Navigator pokaże „bateria panelu: X %” i ostrzeże z wyprzedzeniem.
Wybudzenie: dowolna dźwignia, przycisk albo pokrętło (przerwanie z ekspandera / pinów).

## Procesor i układy

| Blok | Część (MPN — do sprawdzenia z kartą i dostępnością w JLCPCB) |
|---|---|
| Procesor + BLE 5 | Espressif **ESP32‑C3‑MINI‑1‑N4** (antena na module, ta sama rodzina co płytka Maszyna — wspólny kod) |
| Sterownik diod | 2 × Lumissil **IS31FL3236A‑QFLS2** (36 kanałów PWM, I²C) |
| Wejścia (17 dźwigni/przycisków) | 3 × **TCA9534** (ekspander I²C z przerwaniem) albo bezpośrednio piny ESP32‑C3 + 1 ekspander |
| Zasilanie | **TPS62177** (buck 3,3 V, Iq 4,8 µA), MOSFET P przeciw odwrotnej polaryzacji, TVS |
| Diody RGB | 14 × dioda RGB ze wspólną anodą, obudowa 5050 albo przewlekane 5 mm pod soczewką (do wyboru przy obudowie) |
| Czujnik światła | fototranzystor (np. TEMT6000) na ADC |
| Przełączniki sekcji | dźwigniowe IP67 z nakrętką i uszczelką, ON‑OFF — np. APEM seria 600H albo C&K 7000 z uszczelnieniem panelowym (wybór w 22b) |
| START/STOP | przycisk wandaloodporny IP67 Ø 22 mm z pierścieniem RGB |
| Pokrętło | enkoder z przyciskiem w wersji uszczelnionej (np. Bourns PEC11R z uszczelką panelową albo enkoder IP65 do panelu) |

Elementy panelowe (dźwignie, przycisk, enkoder) są przewlekane i wkręcane w ściankę obudowy — w JLCPCB montaż SMD
plus THT; jeśli elementu IP67 nie ma w magazynie JLCPCB, płytka przychodzi bez niego (lutuje się 13 dźwigni ręcznie).

## Obudowa (etap 22c)

- Własny projekt, nowoczesna opływowa bryła (zaokrąglone krawędzie, pochylona płyta czołowa pod kciuk) — druk 3D z ASA,
  uszczelka na całym obwodzie, IP65/IP67 przy dobrze dokręconych nakrętkach przełączników.
- Opisy sekcji 1–13 wytłoczone przy dźwigniach, osłona przed przypadkowym przestawieniem (rant wokół dźwigni).
- Komora baterii 6 × AA od spodu z osobną uszczelką i zatrzaskiem (bez narzędzi).
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
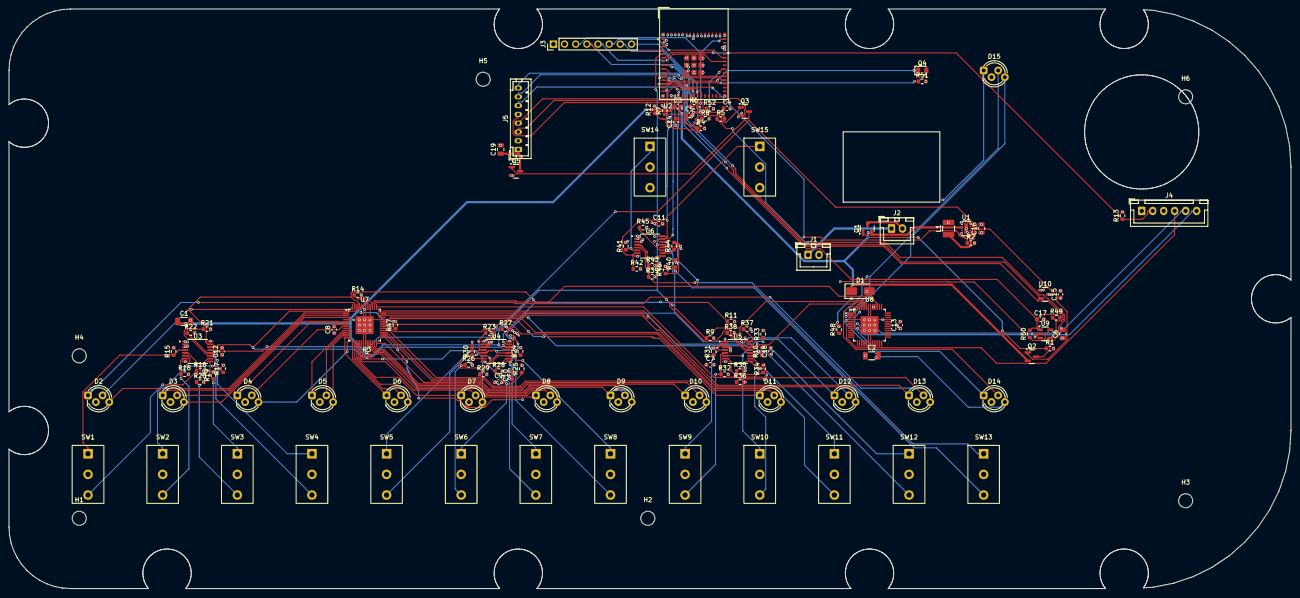
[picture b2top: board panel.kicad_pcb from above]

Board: 4 copper layers, 292.0 x 132.0 mm, 128 parts (0 on the bottom side), 117 nets.

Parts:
C1: 10u 25V; C_1206_3216Metric
C2: 22u 10V; C_1206_3216Metric
C3, C4, C7, C8, C9, C10, C11, C12, C14, C17, C18: 100n; C_0603_1608Metric
C5: 1u; C_0603_1608Metric
C6, C16, C19: 10u; C_0805_2012Metric
C13, C15: 4.7u; C_0603_1608Metric
D1: SMAJ12A; D_SMA
D2: RGB 5mm WA S1; LED_D5.0mm-4_RGB_Staggered_Pins
D3: RGB 5mm WA S2; LED_D5.0mm-4_RGB_Staggered_Pins
D4: RGB 5mm WA S3; LED_D5.0mm-4_RGB_Staggered_Pins
D5: RGB 5mm WA S4; LED_D5.0mm-4_RGB_Staggered_Pins
D6: RGB 5mm WA S5; LED_D5.0mm-4_RGB_Staggered_Pins
D7: RGB 5mm WA S6; LED_D5.0mm-4_RGB_Staggered_Pins
D8: RGB 5mm WA S7; LED_D5.0mm-4_RGB_Staggered_Pins
D9: RGB 5mm WA S8; LED_D5.0mm-4_RGB_Staggered_Pins
D10: RGB 5mm WA S9; LED_D5.0mm-4_RGB_Staggered_Pins
D11: RGB 5mm WA S10; LED_D5.0mm-4_RGB_Staggered_Pins
D12: RGB 5mm WA S11; LED_D5.0mm-4_RGB_Staggered_Pins
D13: RGB 5mm WA S12; LED_D5.0mm-4_RGB_Staggered_Pins
D14: RGB 5mm WA S13; LED_D5.0mm-4_RGB_Staggered_Pins
D15: RGB 5mm WA STAN; LED_D5.0mm-4_RGB_Staggered_Pins
H1, H2, H3, H4, H5, H6: M3; MountingHole_3.2mm_M3
J1: BATERIA 6xAA; JST_XH_B2B-XH-A_1x02_P2.50mm_Vertical
J2: WLACZNIK I/O; JST_XH_B2B-XH-A_1x02_P2.50mm_Vertical
J3: PROG (nie montować); PinHeader_1x08_P2.54mm_Vertical
J4: START/STOP; JST_XH_B6B-XH-A_1x06_P2.50mm_Vertical
J5: E-PAPIER 4.2 SPI; JST_PH_B8B-PH-K_1x08_P2.00mm_Vertical
L1: 2.2u 1A; L_1210_3225Metric
Q1: DMP3099L; SOT-23
Q2: BSS84; SOT-23
Q3: 2N7002; SOT-23
Q4: PT19-21C (0805); LED_0805_2012Metric
Q5: BSS84 (zasilanie EPD); SOT-23
R1, R12, R49, R50, R52: 100k; R_0603_1608Metric
R2, R3, R4, R5, R11, R13, R14, R15, R16, R17, R18, R19, R20, R21, R22, R23, R24, R25, R26, R27, R28, R29, R30, R31, R32, R33, R34, R35, R36, R37, R38, R39, R40, R41, R42, R43, R44, R45, R46: 1M; R_0603_1608Metric
R6: 220k; R_0603_1608Metric
R7, R8, R47, R48, R51: 10k; R_0603_1608Metric
R9, R10: 4.7k; R_0603_1608Metric
SW1: SEKCJA 1 (ON)-OFF-(ON); SW_Toggle_CK7000_PC_P4.70mm
SW2: SEKCJA 2 (ON)-OFF-(ON); SW_Toggle_CK7000_PC_P4.70mm
SW3: SEKCJA 3 (ON)-OFF-(ON); SW_Toggle_CK7000_PC_P4.70mm
SW4: SEKCJA 4 (ON)-OFF-(ON); SW_Toggle_CK7000_PC_P4.70mm
SW5: SEKCJA 5 (ON)-OFF-(ON); SW_Toggle_CK7000_PC_P4.70mm
SW6: SEKCJA 6 (ON)-OFF-(ON); SW_Toggle_CK7000_PC_P4.70mm
SW7: SEKCJA 7 (ON)-OFF-(ON); SW_Toggle_CK7000_PC_P4.70mm
SW8: SEKCJA 8 (ON)-OFF-(ON); SW_Toggle_CK7000_PC_P4.70mm
SW9: SEKCJA 9 (ON)-OFF-(ON); SW_Toggle_CK7000_PC_P4.70mm
SW10: SEKCJA 10 (ON)-OFF-(ON); SW_Toggle_CK7000_PC_P4.70mm
SW11: SEKCJA 11 (ON)-OFF-(ON); SW_Toggle_CK7000_PC_P4.70mm
SW12: SEKCJA 12 (ON)-OFF-(ON); SW_Toggle_CK7000_PC_P4.70mm
SW13: SEKCJA 13 (ON)-OFF-(ON); SW_Toggle_CK7000_PC_P4.70mm
SW14: AUTO ON-OFF; SW_Toggle_CK7000_PC_P4.70mm
SW15: SWIATLO ON-OFF; SW_Toggle_CK7000_PC_P4.70mm
U1: TPS62177DQC; WSON-10-1EP_2x3mm_P0.5mm_EP0.84x2.4mm
U2: ESP32-S3-MINI-1; ESP32-S2-MINI-1
U3, U4, U5, U6: TCA9534; TSSOP-16_4.4x5mm_P0.65mm
U7, U8: IS31FL3236A; TQFP-48-1EP_7x7mm_P0.5mm_EP4.11x4.11mm
U9: TMAG5111C2 (ZY); SOT-23-5
U10: SM351LT; SOT-23

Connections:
BAT_ADC: C4.1, R5.2, R6.1, U2.14
BAT_DIV: Q2.3, R5.1
BAT_EN: Q3.1, R4.1, U2.15
BUCK_SW: L1.1, U1.9
EPD_3V3: C19.1, J5.1, Q5.3
EPD_BUSY: J5.8, U2.35
EPD_CS: J5.5, U2.22
EPD_DC: J5.6, U2.25
EPD_MOSI: J5.3, U2.21
EPD_RST: J5.7, U2.34
EPD_SCK: J5.4, U2.20
EPD_nPWR: Q5.1, R52.1, U2.36
ESP_EN: C5.1, J3.3, R7.1, U2.45
ESP_IO0: J3.4, R8.1, U2.4
ESP_RXD: J3.6, U2.40
ESP_TXD: J3.5, U2.39
EXP3_P4_ZAPAS: R43.1, U6.9
EXP3_P5_ZAPAS: R44.1, U6.10
EXP3_P6_ZAPAS: R45.1, U6.11
EXP3_P7_ZAPAS: R46.1, U6.12
EXP_nINT: R11.1, U2.5, U3.13, U4.13, U5.13, U6.13
GND: C1.2, C2.2, C3.2, C4.2, C5.2, C6.2, C7.2, C8.2, C9.2, C10.2, C11.2, C12.2, C13.2, C14.2, C15.2, C16.2, C17.2, C18.2, C19.2, D1.2, J1.2, J3.2, J4.1, J5.2, Q3.2, R1.2, R4.2, R6.2, R12.2, R14.2, R47.2, R48.2, R51.2, SW1.2, SW2.2, SW3.2, SW4.2, SW5.2, SW6.2, SW7.2, SW8.2, SW9.2, SW10.2, SW11.2, SW12.2, SW13.2, SW14.2, SW15.2, U1.1, U1.6, U1.11, U2.1, U2.2, U2.42, U2.43, U2.46, U2.47, U2.48, U2.49, U2.50, U2.51, U2.52, U2.53, U2.54, U2.55, U2.56, U2.57, U2.58, U2.59, U2.60, U2.61, U2.62, U2.63, U2.64, U2.65, U3.1, U3.2, U3.3, U3.8, U4.2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
I2C_SCL: R10.1, U2.18, U3.14, U4.14, U5.14, U6.14, U7.46, U8.46
I2C_SDA: R9.1, U2.17, U3.15, U4.15, U5.15, U6.15, U7.45, U8.45
ID_PANELU: R12.1, U2.37
LED0_REXT: R47.1, U7.44
LED1_REXT: R48.1, U8.44
LED_D2_B: D2.4, U7.1
LED_D2_G: D2.3, U7.48
LED_D2_R: D2.1, U7.47
LED_D3_B: D3.4, U7.5
LED_D3_G: D3.3, U7.3
LED_D3_R: D3.1, U7.2
LED_D4_B: D4.4, U7.8
LED_D4_G: D4.3, U7.7
LED_D4_R: D4.1, U7.6
LED_D5_B: D5.4, U7.11
LED_D5_G: D5.3, U7.10
LED_D5_R: D5.1, U7.9
LED_D6_B: D6.4, U7.14
LED_D6_G: D6.3, U7.13
LED_D6_R: D6.1, U7.12
LED_D7_B: D7.4, U7.17
LED_D7_G: D7.3, U7.16
LED_D7_R: D7.1, U7.15
LED_D8_B: D8.4, U7.22
LED_D8_G: D8.3, U7.21
LED_D8_R: D8.1, U7.20
LED_D9_B: D9.4, U7.25
LED_D9_G: D9.3, U7.24
LED_D9_R: D9.1, U7.23
LED_D10_B: D10.4, U7.28
LED_D10_G: D10.3, U7.27
LED_D10_R: D10.1, U7.26
LED_D11_B: D11.4, U7.31
LED_D11_G: D11.3, U7.30
LED_D11_R: D11.1, U7.29
LED_D12_B: D12.4, U7.35
LED_D12_G: D12.3, U7.34
LED_D12_R: D12.1, U7.32
LED_D13_B: D13.4, U7.38
LED_D13_G: D13.3, U7.37
LED_D13_R: D13.1, U7.36
LED_D14_B: D14.4, U8.1
LED_D14_G: D14.3, U8.48
LED_D14_R: D14.1, U8.47
LED_D15_B: D15.4, U8.5
LED_D15_G: D15.3, U8.3
LED_D15_R: D15.1, U8.2
LED_SDB: R14.1, U2.19, U7.39, U8.39
P_AUTO: R41.1, SW14.1, U6.6
P_SWIATLO: R42.1, SW15.1, U6.7
Q1_G: Q1.1, R1.1
Q2_G: Q2.1, Q3.3, R3.1
REG_nSLEEP: R2.1, U1.8, U2.16
ROLLER_A: R49.1, U2.9, U9.4
ROLLER_B: R50.1, U2.10, U9.5
ROLLER_WCISK: U2.8, U10.2
ROLLER_ZASIL: C17.1, R49.2, R50.2, U2.11, U9.1
S1_WL: R15.1, SW1.1, U3.4
S1_WYL: R16.1, SW1.3, U3.5
S2_WL: R17.1, SW2.1, U3.6
S2_WYL: R18.1, SW2.3, U3.7
S3_WL: R19.1, SW3.1, U3.9
S3_WYL: R20.1, SW3.3, U3.10
S4_WL: R21.1, SW4.1, U3.11
S4_WYL: R22.1, SW4.3, U3.12
S5_WL: R23.1, SW5.1, U4.4
S5_WYL: R24.1, SW5.3, U4.5
S6_WL: R25.1, SW6.1, U4.6
S6_WYL: R26.1, SW6.3, U4.7
S7_WL: R27.1, SW7.1, U4.9
S7_WYL: R28.1, SW7.3, U4.10
S8_WL: R29.1, SW8.1, U4.11
S8_WYL: R30.1, SW8.3, U4.12
S9_WL: R31.1, SW9.1, U5.4
S9_WYL: R32.1, SW9.3, U5.5
S10_WL: R33.1, SW10.1, U5.6
S10_WYL: R34.1, SW10.3, U5.7
S11_WL: R35.1, SW11.1, U5.9
S11_WYL: R36.1, SW11.3, U5.10
S12_WL: R37.1, SW12.1, U5.11
S12_WYL: R38.1, SW12.3, U5.12
S13_WL: R39.1, SW13.1, U6.4
S13_WYL: R40.1, SW13.3, U6.5
START: J4.2, R13.1, U2.6
START_B: J4.6, U8.8
START_G: J4.5, U8.7
START_R: J4.4, U8.6
SWIATLO_ADC: Q4.2, R51.1, U2.13
SWIATLO_EN: Q4.1, U2.12
USB_DN: J3.7, U2.23
USB_DP: J3.8, U2.24
V3V3: C2.1, C6.1, C7.1, C8.1, C9.1, C10.1, C11.1, C12.1, C13.1, C14.1, C15.1, C16.1, C18.1, D2.2, D3.2, D4.2, D5.2, D6.2, D7.2, D8.2, D9.2, D10.2, D11.2, D12.2, D13.2, D14.2, D15.2, J3.1, J4.3, L1.2, Q5.2, R2.2, R7.2, R8.2, R9.2, R10.2, R11.2, R13.2, R15.2, R16.2, R17.2, R18.2, R19.2, R20.2, R21.2, R22.2, R23.2, R24.2, R25.2, R26.2, R27.2, R28.2, R29.2, R30.2, R31.2, R32.2, R33.2, R34.2, R35.2, R36.2, R37.2, R38.2, R39.2, R40.2, R41.2, R42.2, R43.2, R44.2, R45.2, R46.2, R52.2, U1.5, U1.10, U2.3, U3.16, U4.1, U4.16, U5.2, U5.16, U6.1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
VBAT: J1.1, J2.1
VBAT_SW: J2.2, Q1.3
VIN: C1.1, C3.1, D1.1, Q1.2, Q2.2, R3.2, U1.2, U1.3

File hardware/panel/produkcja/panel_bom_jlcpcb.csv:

Comment,Designator,Footprint,MPN,LCSC Part #
100k,"R1,R12,R49,R50,R52",R_0603_1608Metric,0603WAF1003T5E,C25803
100n,"C3,C4,C7,C8,C9,C10,C11,C12,C14,C17,C18",C_0603_1608Metric,CC0603KRX7R9BB104,C14663
10k,"R7,R8,R47,R48,R51",R_0603_1608Metric,0603WAF1002T5E,C25804
10u,"C6,C16,C19",C_0805_2012Metric,CL21A106KAYNNNE,C15850
10u 25V,C1,C_1206_3216Metric,CL31A106KAHNNNE,
1M,"R2,R3,R4,R5,R11,R13,R14,R15,R16,R17,R18,R19,R20,R21,R22,R23,R24,R25,R26,R27,R28,R29,R30,R31,R32,R33,R34,R35,R36,R37,R38,R39,R40,R41,R42,R43,R44,R45,R46",R_0603_1608Metric,0603WAF1004T5E,C22935
1u,C5,C_0603_1608Metric,CL10B105KO8NNNC,
2.2u 1A,L1,L_1210_3225Metric,"(dławik 2,2 µH ≥1 A, 1210 / 3225 — np. Sunlord SWPA3015S2R2MT po zmianie footprintu)",
220k,R6,R_0603_1608Metric,0603WAF2203T5E,
22u 10V,C2,C_1206_3216Metric,CL31A226KAHNNNE,
2N7002,Q3,SOT-23,2N7002,
4.7k,"R9,R10",R_0603_1608Metric,0603WAF4701T5E,C23162
4.7u,"C13,C15",C_0603_1608Metric,CL10A475KO8NNNC,
AUTO ON-OFF,SW14,SW_Toggle_CK7000_PC_P4.70mm,,
BATERIA 6xAA,J1,JST_XH_B2B-XH-A_1x02_P2.50mm_Vertical,B2B-XH-A(LF)(SN),
BSS84,Q2,SOT-23,BSS84,
BSS84 (zasilanie EPD),Q5,SOT-23,BSS84,
DMP3099L,Q1,SOT-23,DMP3099L-7,
E-PAPIER 4.2 SPI,J5,JST_PH_B8B-PH-K_1x08_P2.00mm_Vertical,B8B-PH-K-S(LF)(SN),
ESP32-S3-MINI-1,U2,ESP32-S2-MINI-1,ESP32-S3-MINI-1-N8,
IS31FL3236A,"U7,U8",TQFP-48-1EP_7x7mm_P0.5mm_EP4.11x4.11mm,IS31FL3236A-TQLS2-TR,
PROG (nie montować),J3,PinHeader_1x08_P2.54mm_Vertical,,
PT19-21C (0805),Q4,LED_0805_2012Metric,PT19-21C/L41/TR8,
RGB 5mm WA S1,D2,LED_D5.0mm-4_RGB_Staggered_Pins,,
RGB 5mm WA S10,D11,LED_D5.0mm-4_RGB_Staggered_Pins,,
RGB 5mm WA S11,D12,LED_D5.0mm-4_RGB_Staggered_Pins,,
RGB 5mm WA S12,D13,LED_D5.0mm-4_RGB_Staggered_Pins,,
RGB 5mm WA S13,D14,LED_D5.0mm-4_RGB_Staggered_Pins,,
RGB 5mm WA S2,D3,LED_D5.0mm-4_RGB_Staggered_Pins,,
RGB 5mm WA S3,D4,LED_D5.0mm-4_RGB_Staggered_Pins,,
RGB 5mm WA S4,D5,LED_D5.0mm-4_RGB_Staggered_Pins,,
RGB 5mm WA S5,D6,LED_D5.0mm-4_RGB_Staggered_Pins,,
RGB 5mm WA S6,D7,LED_D5.0mm-4_RGB_Staggered_Pins,,
RGB 5mm WA S7,D8,LED_D5.0mm-4_RGB_Staggered_Pins,,
RGB 5mm WA S8,D9,LED_D5.0mm-4_RGB_Staggered_Pins,,
RGB 5mm WA S9,D10,LED_D5.0mm-4_RGB_Staggered_Pins,,
RGB 5mm WA STAN,D15,LED_D5.0mm-4_RGB_Staggered_Pins,,
SEKCJA 1 (ON)-OFF-(ON),SW1,SW_Toggle_CK7000_PC_P4.70mm,,
SEKCJA 10 (ON)-OFF-(ON),SW10,SW_Toggle_CK7000_PC_P4.70mm,,
SEKCJA 11 (ON)-OFF-(ON),SW11,SW_Toggle_CK7000_PC_P4.70mm,,
SEKCJA 12 (ON)-OFF-(ON),SW12,SW_Toggle_CK7000_PC_P4.70mm,,
SEKCJA 13 (ON)-OFF-(ON),SW13,SW_Toggle_CK7000_PC_P4.70mm,,
SEKCJA 2 (ON)-OFF-(ON),SW2,SW_Toggle_CK7000_PC_P4.70mm,,
SEKCJA 3 (ON)-OFF-(ON),SW3,SW_Toggle_CK7000_PC_P4.70mm,,
SEKCJA 4 (ON)-OFF-(ON),SW4,SW_Toggle_CK7000_PC_P4.70mm,,
SEKCJA 5 (ON)-OFF-(ON),SW5,SW_Toggle_CK7000_PC_P4.70mm,,
SEKCJA 6 (ON)-OFF-(ON),SW6,SW_Toggle_CK7000_PC_P4.70mm,,
SEKCJA 7 (ON)-OFF-(ON),SW7,SW_Toggle_CK7000_PC_P4.70mm,,
SEKCJA 8 (ON)-OFF-(ON),SW8,SW_Toggle_CK7000_PC_P4.70mm,,
SEKCJA 9 (ON)-OFF-(ON),SW9,SW_Toggle_CK7000_PC_P4.70mm,,
SM351LT,U10,SOT-23,SM351LT,
SMAJ12A,D1,D_SMA,SMAJ12A,
START/STOP,J4,JST_XH_B6B-XH-A_1x06_P2.50mm_Vertical,B6B-XH-A(LF)(SN),
SWIATLO ON-OFF,SW15,SW_Toggle_CK7000_PC_P4.70mm,,
TCA9534,"U3,U4,U5,U6",TSSOP-16_4.4x5mm_P0.65mm,TCA9534PWR,
TMAG5111C2 (ZY),U9,SOT-23-5,TMAG5111C2AQDBVR,
TPS62177DQC,U1,WSON-10-1EP_2x3mm_P0.5mm_EP0.84x2.4mm,TPS62177DQCR,
WLACZNIK I/O,J2,JST_XH_B2B-XH-A_1x02_P2.50mm_Vertical,B2B-XH-A(LF)(SN),
